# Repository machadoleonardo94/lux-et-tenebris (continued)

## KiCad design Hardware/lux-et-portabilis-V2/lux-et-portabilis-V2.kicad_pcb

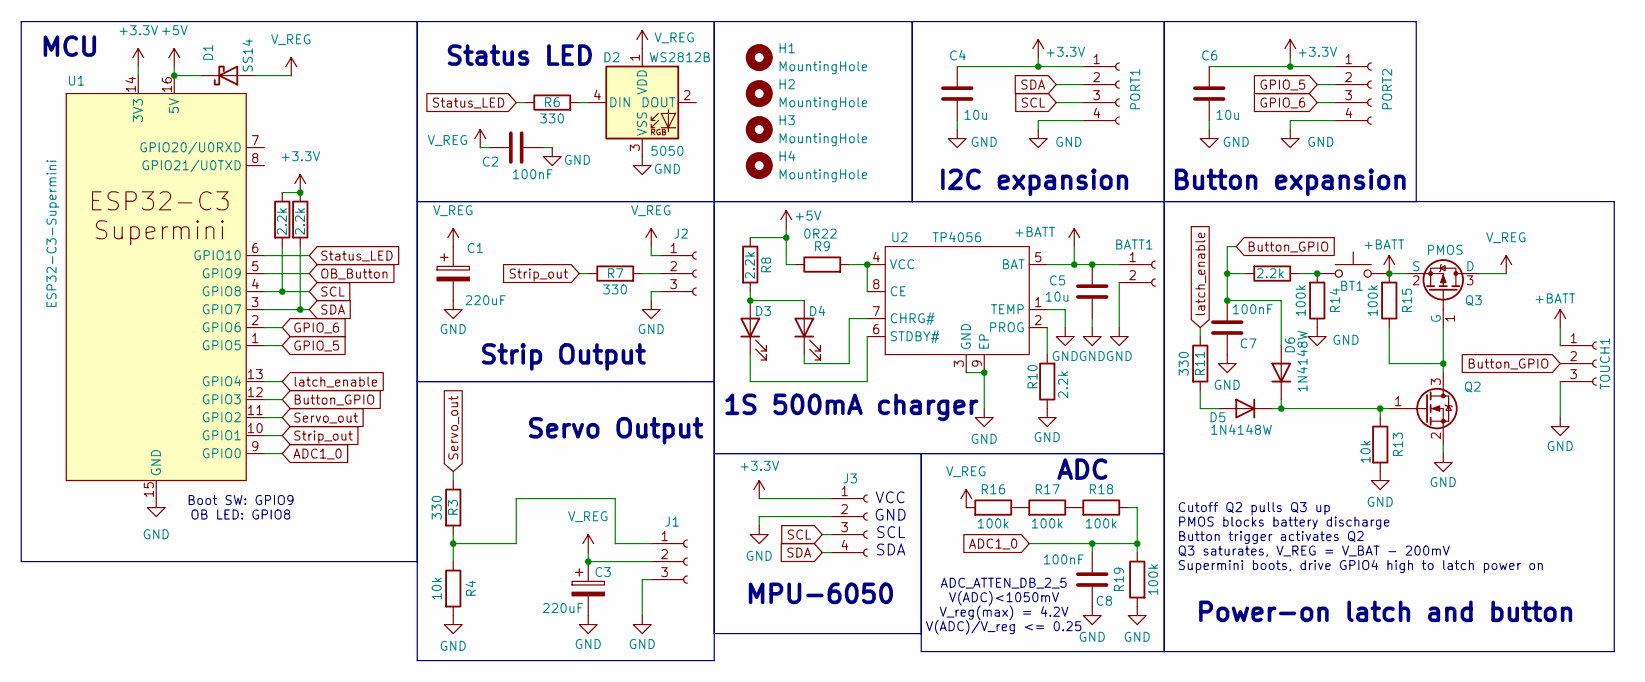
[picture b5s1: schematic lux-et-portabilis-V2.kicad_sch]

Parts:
BATT1: Conn_01x02_Socket; Molex_KK-254_AE-6410-02A_1x02_P2.54mm_Vertical; LCSC C49023803
BT1: SW_Push; SW_SPST_PTS647_Sx38; LCSC C455246
C1, C3: 220uF; CP_Elec_6.3x7.7; Mfr. Part Number 35TKV220M8X10.5; LCSC C25170691
C2, C7, C8: 100nF; C_0805_2012Metric; Mfr. Part Number CC0805KRX7R9BB104; LCSC C49678
C4, C5, C6: 10u; C_0805_2012Metric; LCSC C15850
D1: SS14; D_SMA; LCSC C2480
D2: WS2812B; LED_WS2812B_PLCC4_5.0x5.0mm_P3.2mm; LCSC C2843785
D3: LED_BLUE; LED_0805_2012Metric_Pad1.15x1.40mm_HandSolder; LCSC C965817
D4: LED_RED; LED_0805_2012Metric_Pad1.15x1.40mm_HandSolder; LCSC C84256
D5, D6: 1N4148W; D_SOD-123; Mfr. Part Number 1N4148W-7-F; LCSC C83528
H1, H2, H3, H4: MountingHole; MountingHole_3.2mm_M3
J1: Conn_01x03_Socket; PinHeader_1x03_P2.54mm_Vertical
J2: Conn_01x03_Socket; TerminalBlock_Xinya_XY308-2.54-3P_1x03_P2.54mm_Horizontal
J3: Conn_01x04_Socket; MPU6050
PORT1, PORT2: Conn_01x04_Socket; Hirose_DF13C_CL535-0404-8-51_1x04-1MP_P1.25mm_Vertical; LCSC C7433470
Q2: 2N7002K; SOT-23; LCSC C65189
Q3: PMOS; SOT-23_Handsoldering; LCSC C42456992
R1, R2, R8, R10, R12: 2.2k; R_0805_2012Metric; LCSC C17520
R3, R6, R7, R11: 330; R_0805_2012Metric; LCSC C17630
R4, R13: 10k; R_0805_2012Metric; LCSC C17414
R9: 0R22; R_1206_3216Metric_Pad1.30x1.75mm_HandSolder; LCSC C2683384
R14, R15, R16, R17, R18, R19: 100k; R_0805_2012Metric; LCSC C149504
TOUCH1: Conn_01x03_Socket; PinHeader_1x03_P2.54mm_Vertical
U1: ESP32-C3-Supermini
U2: TP4056; ESOP-8_L4.9-W3.9-P1.27-LS6.0-BL-EP; LCSC Part Name 1A锂电池充电IC

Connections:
+3.3V: C4.1, C6.1, J3.1, PORT1.1, PORT2.1, R1.1, R2.1, U1.14 (3V3)
+5V: D1.1 (K), R8.1, R9.1, U1.16 (5V)
+BATT: BATT1.1, BT1.1, C5.1, Q3.2 (S), R15.2, TOUCH1.1, U2.5 (BAT)
ADC1_0: C8.2, R18.1, R19.1, U1.9 (GPIO0)
Button_GPIO: C7.2, D6.2 (A), R12.2, TOUCH1.2, U1.12 (GPIO3)
GND: BATT1.2, C1.2, C2.2, C3.2, C4.2, C5.2, C6.2, C7.1, C8.1, D2.3 (VSS), J1.3, J2.3, J3.2, PORT1.4, PORT2.4, Q2.2 (S), R4.2, R10.1, R13.2, R14.1, R19.2, TOUCH1.3, U1.15 (GND), U2.1 (TEMP), U2.3 (GND), U2.9 (EP)
GPIO_5: PORT2.2, U1.1 (GPIO5)
GPIO_6: PORT2.3, U1.2 (GPIO6)
unnamed: BT1.2, R12.1, R14.2
unnamed: D2.4 (DIN), R6.2
unnamed: D3.2 (A), D4.2 (A), R8.2
unnamed: D3.1 (K), U2.6 (STDBY#)
unnamed: D4.1 (K), U2.7 (CHRG#)
unnamed: D5.2 (A), R11.2
unnamed: D5.1 (K), D6.1 (K), Q2.1 (G), R13.1
unnamed: J1.1, R3.2, R4.1
unnamed: J2.2, R7.2
unnamed: Q2.3 (D), Q3.1 (G), R15.1
unnamed: R16.1, R17.2
unnamed: R17.1, R18.2
unnamed: R9.2, U2.4 (VCC), U2.8 (CE)
unnamed: R10.2, U2.2 (PROG)
OB_Button: U1.5 (GPIO9)
SCL: J3.3, PORT1.3, R1.2, U1.4 (GPIO8)
SDA: J3.4, PORT1.2, R2.2, U1.3 (GPIO7)
Servo_out: R3.1, U1.11 (GPIO2)
Status_LED: R6.1, U1.6 (GPIO10)
Strip_out: R7.1, U1.10 (GPIO1)
V_REG: C1.1, C2.1, C3.1, D1.2 (A), D2.1 (VDD), J1.2, J2.1, Q3.3 (D), R16.2
latch_enable: R11.1, U1.13 (GPIO4)

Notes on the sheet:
Strip Output
ADC_ATTEN_DB_2_5 V(ADC)<1050mV V_reg(max) = 4.2V V(ADC)/V_reg <= 0.25
I2C expansion
Power-on latch and button
MCU
MPU-6050
Status LED
ADC
Boot SW: GPIO9 OB LED: GPIO8
Cutoff Q2 pulls Q3 up PMOS blocks battery discharge Button trigger activates Q2 Q3 saturates, V_REG = V_BAT - 200mV Supermini boots, drive GPIO4 high to latch power on
1S 500mA charger
Button expansion
Servo Output
VCC GND SCL SDA

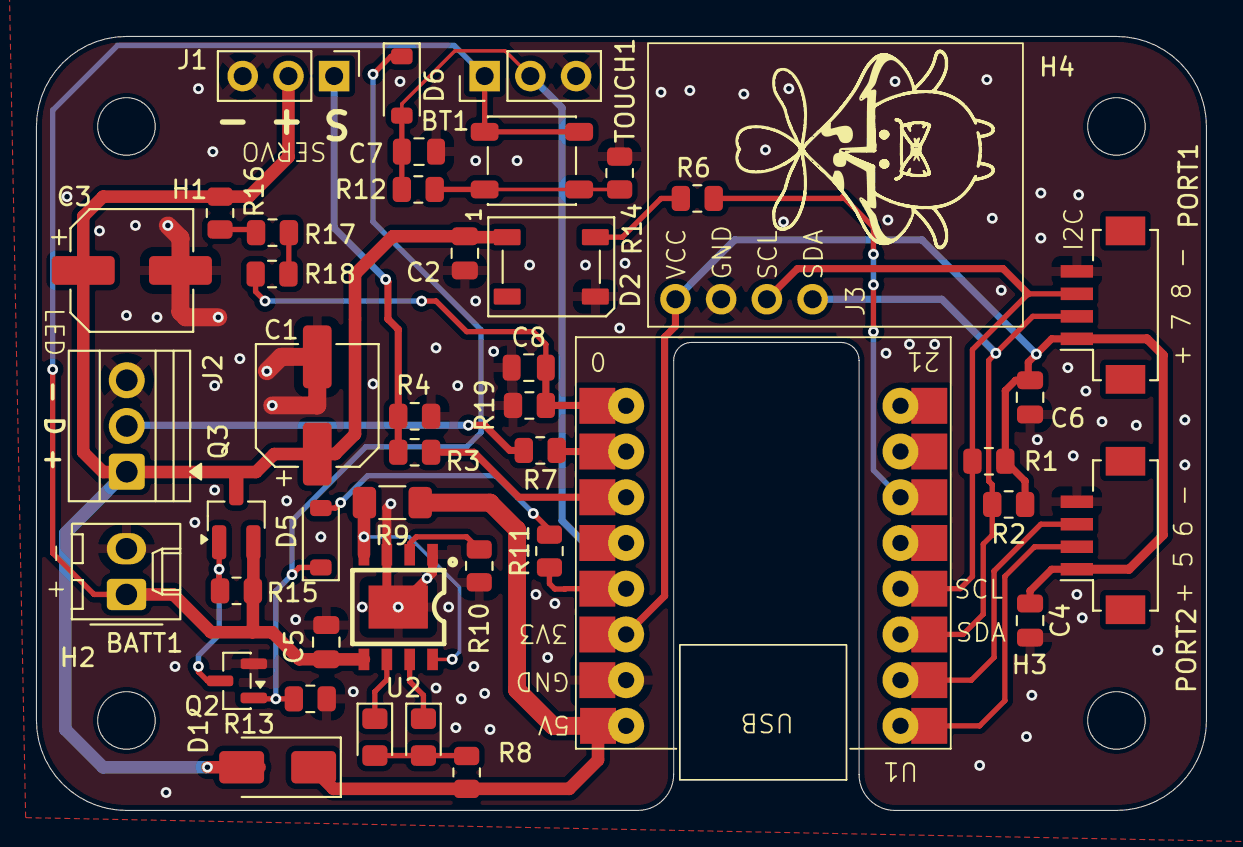
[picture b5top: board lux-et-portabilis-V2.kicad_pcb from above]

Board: 2 copper layers, 65.0 x 43.0 mm, 48 parts (0 on the bottom side), 29 nets.

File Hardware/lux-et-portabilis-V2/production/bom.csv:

Designator,Footprint,Quantity,Value,LCSC Part #
BT1,SW_SPST_PTS647_Sx38,1,SW_Push,C455246
"C1, C3",CP_Elec_6.3x7.7,2,220uF,C25170691
"C2, C7, C8",0805,3,100nF,C49678
"C4, C5, C6",0805,3,10u,C15850
D1,D_SMA,1,SS14,C2480
D2,LED_WS2812B_PLCC4_5.0x5.0mm_P3.2mm,1,WS2812B,C2843785
D3,0805,1,LED_BLUE,C965817
D4,0805,1,LED_RED,C84256
"D5, D6",D_SOD-123,2,1N4148W,C83528
"J1, TOUCH1",PinHeader_1x03_P2.54mm_Vertical,2,Conn_01x03_Socket,
J2,TerminalBlock_Xinya_XY308-2.54-3P_1x03_P2.54mm_Horizontal,1,Conn_01x03_Socket,
J3,MPU6050,1,Conn_01x04_Socket,
"PORT1, PORT2",Hirose_DF13C_CL535-0404-8-51_1x04-1MP_P1.25mm_Vertical,2,Conn_01x04_Socket,C7433470
Q2,SOT-23,1,2N7002K,C65189
Q3,SOT-23_Handsoldering,1,PMOS,C42456992
"R1, R10, R12, R2, R8",0805,5,2.2k,C17520
"R11, R3, R6, R7",0805,4,330,C17630
"R13, R4",0805,2,10k,C17414
"R14, R15, R16, R17, R18, R19",0805,6,100k,C149504
R9,1206,1,0R22,C2683384
U1,ESP32-C3-Supermini,1,ESP32-C3-Supermini,
U2,ESOP-8_L4.9-W3.9-P1.27-LS6.0-BL-EP,1,TP4056,C382139

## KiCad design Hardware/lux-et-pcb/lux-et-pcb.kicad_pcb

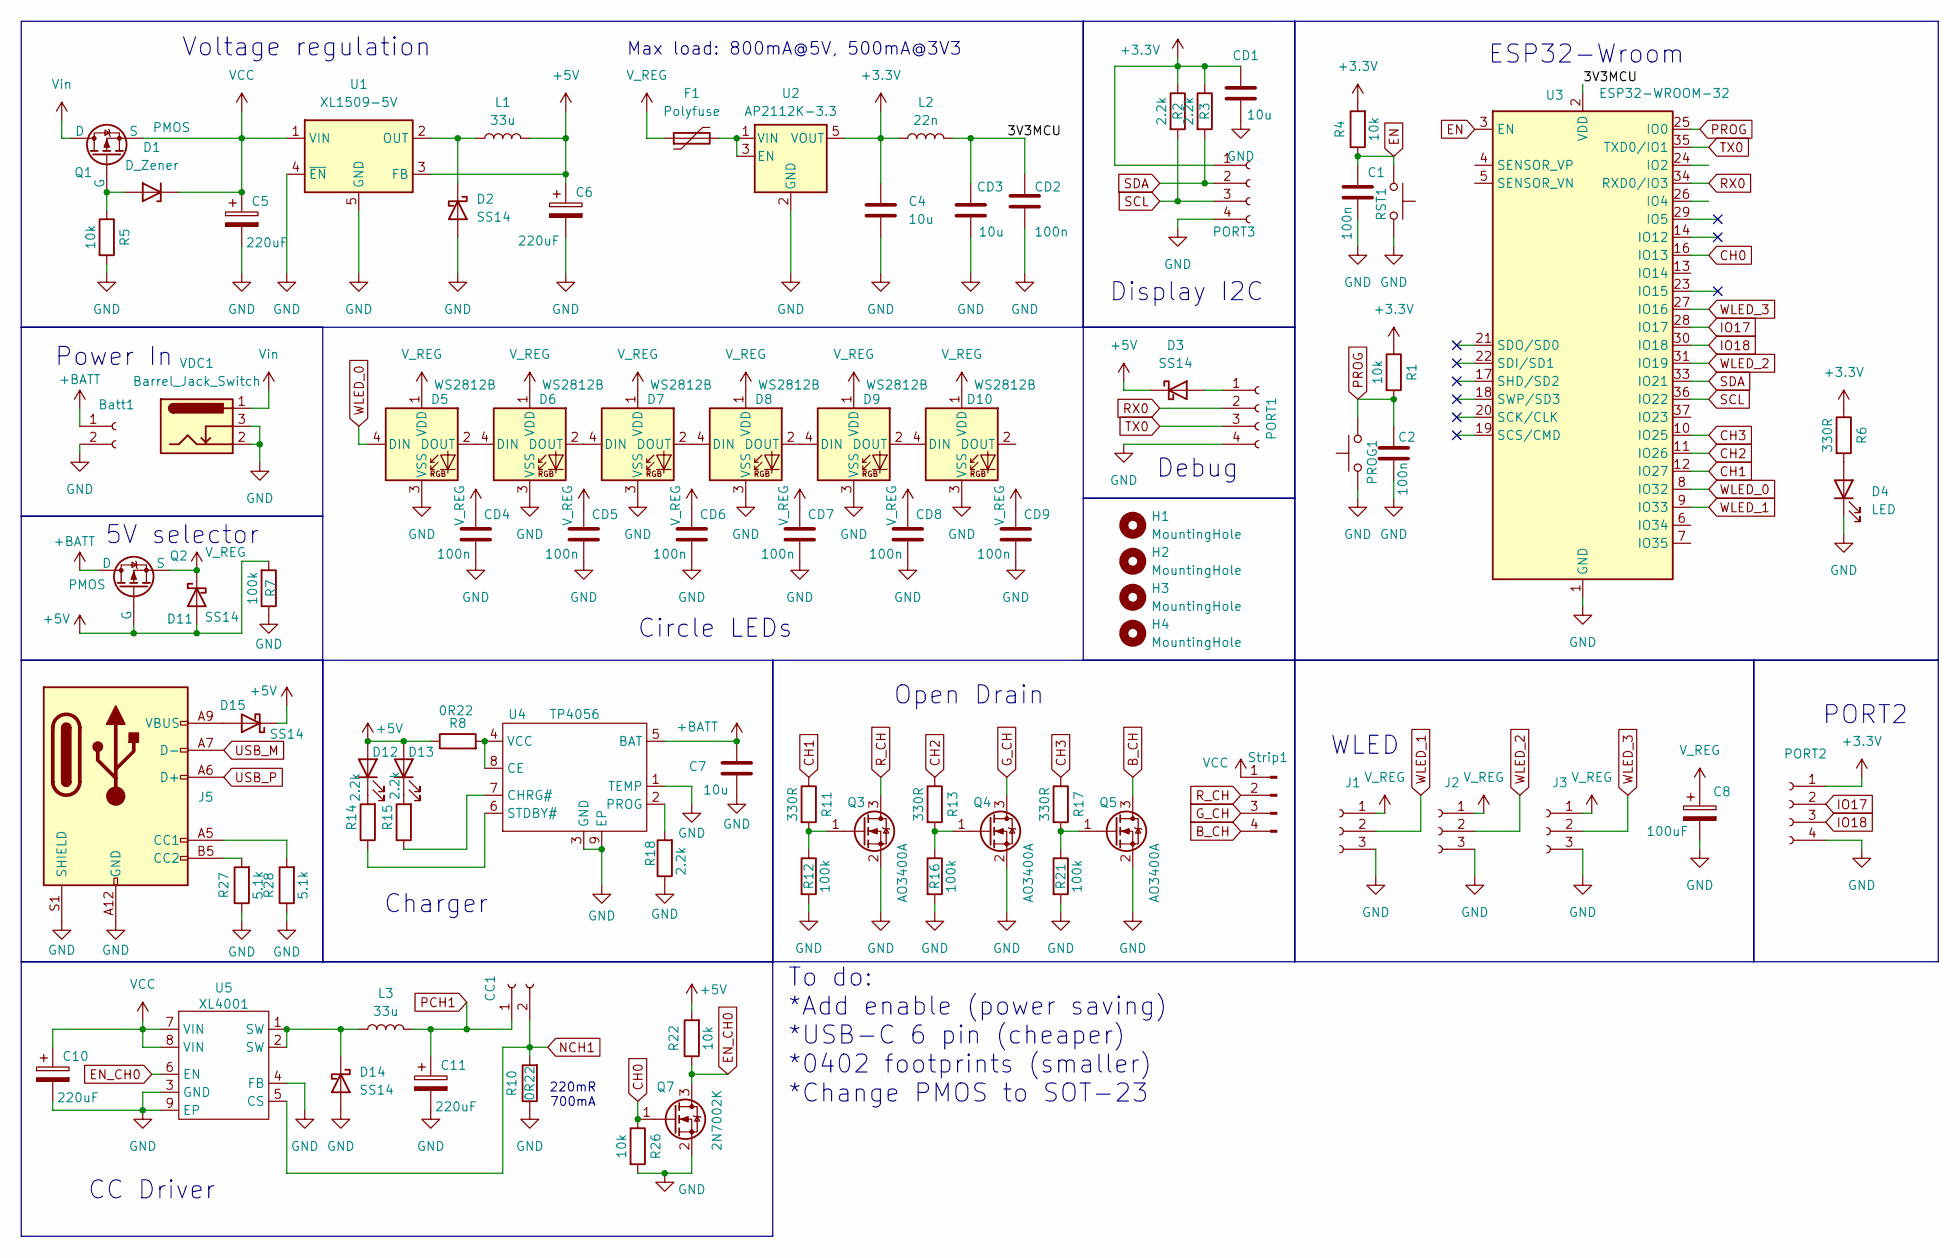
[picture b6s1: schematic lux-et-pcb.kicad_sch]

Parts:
Batt1: Conn_01x02_Socket; Molex_KK-254_AE-6410-02A_1x02_P2.54mm_Vertical; LCSC C49023803
C1, C2: 100n; C_0805_2012Metric; LCSC C2909631
C4, C7: 10u; C_0805_2012Metric; LCSC C380331
C5, C6, C10, C11: 220uF; C_Elec_6.3x7.7; LCSC C7471881
C8: 100uF; C_Elec_6.3x7.7; LCSC C99837
CC1: Conn_01x02_Socket; Molex_KK-254_AE-6410-02A_1x02_P2.54mm_Vertical; LCSC C49023803
CD1, CD3: 10u; C_0805_2012Metric; LCSC C380331
CD2, CD4, CD5, CD6, CD7, CD8, CD9: 100n; C_0805_2012Metric; LCSC C2909631
D1: D_Zener; D_MiniMELF; LCSC C181075
D2, D3, D11, D14, D15: SS14; D_SMA; LCSC C2909920
D4: LED; LED_0805_2012Metric_Pad1.15x1.40mm_HandSolder; LCSC C84256
D5, D6, D7, D8, D9, D10: WS2812B; LED_WS2812B_PLCC4_5.0x5.0mm_P3.2mm; LCSC C2843785
D12: LED_BLUE; LED_0805_2012Metric_Pad1.15x1.40mm_HandSolder; LCSC C965817
D13: LED_RED; LED_0805_2012Metric_Pad1.15x1.40mm_HandSolder; LCSC C84256
F1: Polyfuse; Fuse_1206_3216Metric_Pad1.42x1.75mm_HandSolder; LCSC C22446878
H1, H2, H3, H4: MountingHole; MountingHole_3.2mm_M3
J1, J2, J3: Conn_01x03_Socket; TerminalBlock_Xinya_XY308-2.54-3P_1x03_P2.54mm_Horizontal
J5: USB_C_Receptacle_USB2.0_8P; USB-C-SMD_GT-USB-7101A; LCSC C7469647
L1, L3: 33u; L_Sunlord_SWPA4010S; LCSC C167885
L2: 22n; L_0805_2012Metric; LCSC C108962
PORT1, PORT2, PORT3: Conn_01x04_Socket; Hirose_DF13C_CL535-0404-8-51_1x04-1MP_P1.25mm_Vertical; LCSC C7433470
PROG1: SW_Push; SW_SPST_PTS647_Sx38; LCSC C2888502
Q1, Q2: PMOS; SOT-223-3_TabPin2; LCSC C154901
Q3, Q4, Q5: AO3400A; SOT-23; LCSC C347497
Q7: 2N7002K; SOT-23; LCSC C65189
R1, R4, R5, R22, R26: 10k; R_0805_2012Metric; LCSC C17414
R2, R3, R14, R15, R18: 2.2k; R_0805_2012Metric; LCSC C17520
R6, R11, R13, R17: 330R; R_0805_2012Metric; LCSC C17630
R7, R12, R16, R21: 100k; R_0805_2012Metric; LCSC C149504
R8, R10: 0R22; R_2010_5025Metric; LCSC C2999625
R27, R28: 5.1k; R_0805_2012Metric; LCSC C27834
RST1: SW_Push; SW_SPST_PTS647_Sx38; LCSC C2888502
Strip1: Conn_01x02_Pin; TerminalBlock_Xinya_XY308-2.54-4P_1x04_P2.54mm_Horizontal; LCSC 1
U1: XL1509-5V; SOIC-8_3.9x4.9mm_P1.27mm; LCSC C2681227
U2: AP2112K-3.3; SOT-23-5; LCSC C51118
U3: ESP32-WROOM-32; ESP32-WROOM-32U; LCSC C2980301
U4: TP4056; SOP-8_L4.9-W3.9-P1.27-LS6.0-BL-EP; Manufacturer Part TP4056; LCSC Part Name 1A锂电池充电IC
U5: XL4001; ESOP-8_L4.9-W3.9-P1.27-LS6.0-BL-EP; Manufacturer Part XL4001E1; LCSC Part Name XL4001E1
VDC1: Barrel_Jack_Switch; BarrelJack_Horizontal; LCSC C720557

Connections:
+3.3V: C4.1, CD1.1, L2.1, PORT2.1, PORT3.1, R1.1, R2.1, R3.1, R4.2, R6.1, U2.5 (VOUT)
+5V: C6.1, D3.1 (K), D11.2 (A), D12.2 (A), D13.2 (A), D15.1 (K), L1.2, Q2.2 (G), R7.2, R8.1, R22.2, U1.3 (FB)
+BATT: Batt1.1, C7.1, Q2.1 (D), U4.5 (BAT)
/3V3MCU: CD2.1, CD3.1, L2.2, U3.2 (VDD)
B_CH: Q5.3 (D), Strip1.4
CH0: Q7.1 (G), R26.1, U3.16 (IO13)
CH1: R11.1, U3.12 (IO27)
CH2: R13.1, U3.11 (IO26)
CH3: R17.1, U3.10 (IO25)
EN: C1.1, R4.1, RST1.2, U3.3 (EN)
EN_CH0: Q7.3 (D), R22.1, U5.6 (EN)
GND: Batt1.2, C1.2, C2.2, C4.2, C5.2, C6.2, C7.2, C8.2, C10.2, C11.2, CD1.2, CD2.2, CD3.2, CD4.2, CD5.2, CD6.2, CD7.2, CD8.2, CD9.2, D2.2 (A), D4.1 (K), D5.3 (VSS), D6.3 (VSS), D7.3 (VSS), D8.3 (VSS), D9.3 (VSS), D10.3 (VSS), D14.2 (A), J1.3, J2.3, J3.3, J5.A12 (GND), J5.B12 (GND), J5.S1 (SHIELD), PORT1.4, PORT2.4, PORT3.4, PROG1.1, Q3.2 (S), Q4.2 (S), Q5.2 (S), Q7.2 (S), R5.2, R7.1, R10.1, R12.2, R16.2, R18.1, R21.2, R26.2, R27.1, R28.1, RST1.1, U1.4 (~EN), U1.5 (GND), U1.6 (GND), U1.7 (GND), U1.8 (GND), U2.2 (GND), U3.1 (GND), U3.15 (GND), U3.38 (GND), U3.39 (GND), U4.1 (TEMP), U4.3 (GND), U4.9 (EP), U5.3 (GND), U5.4 (FB), U5.9 (EP), VDC1.2, VDC1.3
G_CH: Q4.3 (D), Strip1.3
IO17: PORT2.2, U3.28 (IO17)
IO18: PORT2.3, U3.30 (IO18)
NCH1: CC1.2, R10.2, U5.5 (CS)
unnamed: D1.2 (A), Q1.2 (G), R5.1
unnamed: D2.1 (K), L1.1, U1.2 (OUT)
unnamed: D3.2 (A), PORT1.1
unnamed: D4.2 (A), R6.2
unnamed: D5.2 (DOUT), D6.4 (DIN)
unnamed: D6.2 (DOUT), D7.4 (DIN)
unnamed: D7.2 (DOUT), D8.4 (DIN)
unnamed: D8.2 (DOUT), D9.4 (DIN)
unnamed: D9.2 (DOUT), D10.4 (DIN)
unnamed: D12.1 (K), R14.2
unnamed: D13.1 (K), R15.2
unnamed: D14.1 (K), L3.1, U5.1 (SW), U5.2 (SW)
unnamed: D15.2 (A), J5.A9 (VBUS), J5.B9 (VBUS)
unnamed: J5.A5 (CC1), R28.2
unnamed: J5.B5 (CC2), R27.2
unnamed: Q3.1 (G), R11.2, R12.1
unnamed: Q4.1 (G), R13.2, R16.1
unnamed: Q5.1 (G), R17.2, R21.1
unnamed: F1.2, U2.1 (VIN), U2.3 (EN)
unnamed: R8.2, U4.4 (VCC), U4.8 (CE)
unnamed: R15.1, U4.7 (CHRG#)
unnamed: R18.2, U4.2 (PROG)
unnamed: R14.1, U4.6 (STDBY#)
PCH1: C11.1, CC1.1, L3.2
PROG: C2.1, PROG1.2, R1.2, U3.25 (IO0)
RX0: PORT1.2, U3.34 (RXD0/IO3)
R_CH: Q3.3 (D), Strip1.2
SCL: PORT3.3, R2.2, U3.36 (IO22)
SDA: PORT3.2, R3.2, U3.33 (IO21)
TX0: PORT1.3, U3.35 (TXD0/IO1)
USB_M: J5.A7 (D-)
USB_P: J5.A6 (D+)
VCC: C5.1, C10.1, D1.1 (K), Q1.3 (S), Strip1.1, U1.1 (VIN), U5.7 (VIN), U5.8 (VIN)
V_REG: C8.1, CD4.1, CD5.1, CD6.1, CD7.1, CD8.1, CD9.1, D5.1 (VDD), D6.1 (VDD), D7.1 (VDD), D8.1 (VDD), D9.1 (VDD), D10.1 (VDD), D11.1 (K), F1.1, J1.1, J2.1, J3.1, Q2.3 (S)
Vin: Q1.1 (D), VDC1.1
WLED_0: D5.4 (DIN), U3.8 (IO32)
WLED_1: J1.2, U3.9 (IO33)
WLED_2: J2.2, U3.31 (IO19)
WLED_3: J3.2, U3.27 (IO16)

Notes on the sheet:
Debug
To do: *Add enable (power saving) *USB-C 6 pin (cheaper) *0402 footprints (smaller) *Change PMOS to SOT-23
PORT2
220mR 700mA
Voltage regulation
Open Drain
ESP32-Wroom
5V selector
Display I2C
Power In
Max load: 800mA@5V, 500mA@3V3
CC Driver
Circle LEDs
Charger
WLED

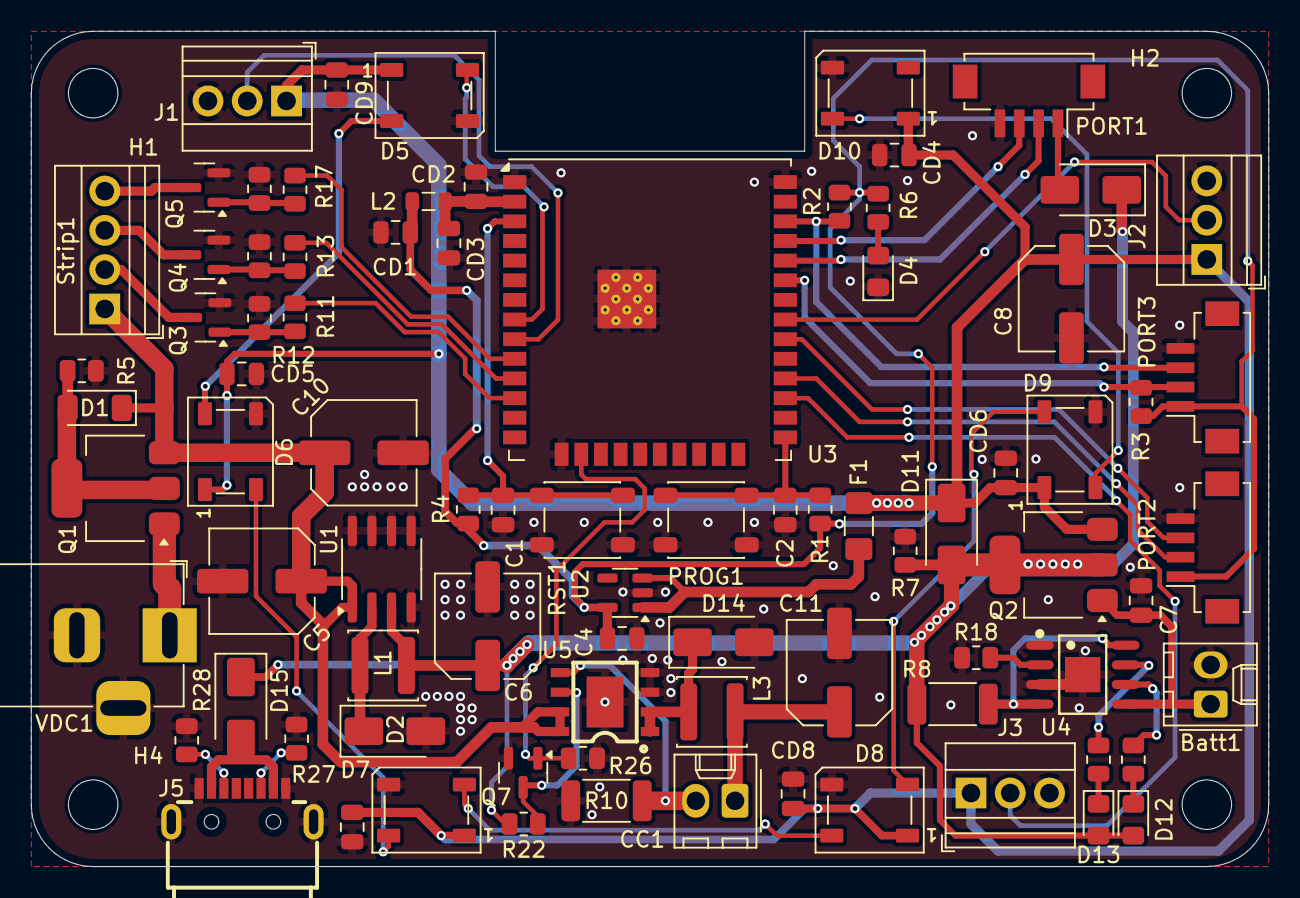
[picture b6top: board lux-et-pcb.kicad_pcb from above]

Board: 2 copper layers, 80.0 x 54.0 mm, 87 parts (0 on the bottom side), 53 nets.

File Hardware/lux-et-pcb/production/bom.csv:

Designator,Footprint,Quantity,Value,LCSC Part #
"BATT1, CC1",Molex_KK-254_AE-6410-02A_1x02_P2.54mm_Vertical,2,Conn_01x02_Socket,C49023803
"C1, C2, CD2, CD4, CD5, CD6, CD7, CD8, CD9",0805,9,100n,C2909631
"C10, C11, C5, C6",C_Elec_6.3x7.7,4,220uF,C7471881
"C4, C7, CD1, CD3",0805,4,10u,C380331
C8,C_Elec_6.3x7.7,1,100uF,C99837
D1,D_MiniMELF,1,D_Zener,C181075
"D10, D5, D6, D7, D8, D9",LED_WS2812B_PLCC4_5.0x5.0mm_P3.2mm,6,WS2812B,C2843785
"D11, D14, D15, D2, D3",D_SMA,5,SS14,C2909920
D12,0805,1,LED_BLUE,C965817
D13,0805,1,LED_RED,C84256
D4,0805,1,LED,C84256
F1,1206,1,Polyfuse,C22446878
"J1, J2, J3",TerminalBlock_Xinya_XY308-2.54-3P_1x03_P2.54mm_Horizontal,3,Conn_01x03_Socket,
J5,USB-C-SMD_GT-USB-7101A,1,USB_C_Receptacle_USB2.0_8P,C7469647
"L1, L3",L_Sunlord_SWPA4010S,2,33u,C167885
L2,0805,1,22n,C108962
"PORT1, PORT2, PORT3",Hirose_DF13C_CL535-0404-8-51_1x04-1MP_P1.25mm_Vertical,3,Conn_01x04_Socket,C7433470
"PROG1, RST1",SW_SPST_PTS647_Sx38,2,SW_Push,C2888502
"Q1, Q2",SOT-223-3_TabPin2,2,PMOS,C154901
"Q3, Q4, Q5",SOT-23,3,AO3400A,C347497
Q7,SOT-23,1,2N7002K,C65189
"R1, R22, R26, R4, R5",0805,5,10k,C17414
"R10, R8",2010,2,0R22,C2999625
"R11, R13, R17, R6",0805,4,330,C17630
"R12, R16, R21, R7",0805,4,100k,C149504
"R14, R15",0805,2,1k,C11702
"R18, R2, R3",0805,3,2k2,C17520
"R27, R28",0805,2,5.1k,C27834
STRIP1,TerminalBlock_Xinya_XY308-2.54-4P_1x04_P2.54mm_Horizontal,1,Conn_01x02_Pin,1
U1,SOIC-8_3.9x4.9mm_P1.27mm,1,XL1509-5V,C2681227
U2,SOT-23-5,1,AP2112K-3.3,C51118
U3,ESP32-WROOM-32U,1,ESP32-WROOM-32,C2980301
U4,SOP-8_L4.9-W3.9-P1.27-LS6.0-BL-EP,1,TP4056,C382139
U5,ESOP-8_L4.9-W3.9-P1.27-LS6.0-BL-EP,1,~,C2988027
VDC1,BarrelJack_Horizontal,1,Barrel_Jack_Switch,C720557

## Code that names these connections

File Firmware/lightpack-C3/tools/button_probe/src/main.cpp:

//? ---------------------- BUTTON PROBE ----------------------
//? A diagnostics-only sketch for the Lux et Portabilis V2 button net.
//? Build and flash it with, from the firmware directory:
//?     pio run -d tools/button_probe -t upload --upload-port COM6
//? It is NOT part of the firmware: this directory is its own PlatformIO project
//* (see platformio.ini here), so the real firmware is not compiled into it.

//! WHY THIS EXISTS
//! The touch pad is an EXTERNAL module on TOUCH1, and the V2 board puts no pull
//! resistor on that net. Measured off the board's own net table:
//!
//!   TOUCH1 pin 1 -> +BATT          (the raw battery rail, NOT 3.3 V)
//!   TOUCH1 pin 2 -> Button_GPIO    (the module's OUT)
//!   TOUCH1 pin 3 -> GND
//!   Button_GPIO  -> ESP32-C3 pad 12 = GPIO3, and nothing else drives it:
//!                   C7  100 nF to GND   (filter)
//!                   R12 2.2 k to BT1    (the on-board power button shares this net)
//!                   D6  1N4148W         (clamp, anode on this net)
//!
//! So the idle level of GPIO3 is entirely the module's business. The firmware
//! assumes ACTIVE HIGH - button_input_configure() gives it INPUT_PULLDOWN and
//* setup_button_interrupt() waits for a RISING edge. A module that is active-LOW
//! or open-drain can never produce that rising edge, and the button then looks
//* completely dead while being perfectly wired.

//! HOW TO READ THIS
//! Each pin is sampled for PROBE_WINDOW_MS under three internal pull
//! configurations in turn. Every window reports the digital levels seen, how many
//! times the level changed, and the average ADC reading in millivolts.
//!
//! Touch the module during EVERY window, then compare:
//!
//!   Only the PULLDOWN window shows edges, min=0 max=1
//!       -> active HIGH, push-pull. The firmware's assumption is correct and the
//!          fault is elsewhere (power to the module, or the module itself).
//!
//!   Only the PULLUP window shows edges, min=0 max=1
//!       -> active LOW / open drain. The firmware needs active_high = false,
//!          which also switches it to INPUT_PULLUP (see services/readings.h).
//!
//!   Edges in NO window, level pinned at 0 or 1
//!       -> the pin never moves. The module is unpowered, its OUT is not on
//!          TOUCH1 pin 2, or it is dead. Check VCC at TOUCH1 pin 1 - remember it
//!          is +BATT, so on USB with no cell fitted it may not be what you expect.
//!
//!   Every window wanders between 0 and 1 with no touch, and the average ADC
//!   reading drifts when your hand approaches
//!       -> nothing is attached to that pin. It is floating.
//!
//!   A fixed average near 1650 mV that never reaches 0 or 3.3 V
//!       -> two resistors are fighting over the line. That is the signature of an
//!          external pull meeting the internal one, and it explains a pin that
//!          reads a constant HIGH or LOW no matter what the module does.
//!
//! GPIO2 is probed as well, as a CONTROL. On this board pad 11 is Servo_out, so
//? it is expected to look like nothing or like a floating pin - it is there to
//* show what "no button here" looks like next to the real pin.

//! SAFETY - GPIO4
//! GPIO4 is latch_enable: it holds the board's own power latch closed. The real
//! firmware raises it in the first statements of setup(), and this sketch does the
//! same. Without it the latch opens and the board switches itself off as soon as
//* the power button is released, which looks exactly like a crash.

#include <Arduino.h>

#define LATCH_ENABLE_PIN 4
#define BUTTON_PIN 3 // TOUCH1 pin 2, the module's OUT, shared with BT1 through R12
#define CONTROL_PIN 2 // Servo_out on V2 - no button here, for contrast

//* How long each pull configuration is held before the report moves on.
#define PROBE_WINDOW_MS 2000
//* Sampling period inside a window. 2 ms is well under any module's output
//* transition and gives ~1000 samples per window.
#define PROBE_SAMPLE_MS 2
//* Discarded after a configuration change: the pin and the 100 nF cap on it need
//! a moment to settle, and those samples would be counted as edges otherwise.
#define PROBE_SETTLE_MS 40

enum probePull : uint8_t
{
    PULL_FLOAT = 0,
    PULL_UP,
    PULL_DOWN,
    PULL_COUNT
};

const char *pull_name(uint8_t cfg)
{
    switch (cfg)
    {
    case PULL_FLOAT:
        return "float   ";
    case PULL_UP:
        return "pullup  ";
    default:
        return "pulldown";
    }
}

void probe_apply_pull(uint8_t pin, uint8_t cfg)
{
    switch (cfg)
    {
    case PULL_UP:
        pinMode(pin, INPUT_PULLUP);
        break;
    case PULL_DOWN:
        pinMode(pin, INPUT_PULLDOWN);
        break;
    default:
        //? INPUT, not INPUT_PULLUP: this window has to show what the outside
        //* world does with the pin when nothing on the chip helps it.
        pinMode(pin, INPUT);
        break;
    }
}

//* One window: hold one pull configuration and report what the pin did.
//? `edges` is the count of digital level changes, so a pin that follows the
//? module produces edges in the window whose pull matches the module's idle
//* state, and a pin that never moves produces none anywhere.
void probe_window(uint8_t pin, uint8_t cfg)
{
    probe_apply_pull(pin, cfg);
    delay(PROBE_SETTLE_MS);

    int first = digitalRead(pin);
    int sawLow = (first == LOW) ? 1 : 0;
    int sawHigh = (first == HIGH) ? 1 : 0;
    int edges = 0;
    int previous = first;

    uint32_t samples = 0;
    uint32_t mv_sum = 0;

    const uint32_t start = millis();
    while (millis() - start < (uint32_t)PROBE_WINDOW_MS)
    {
        const int level = digitalRead(pin);
        if (level != previous)
        {
            edges++;
            previous = level;
        }
        if (level == LOW)
            sawLow = 1;
        else
            sawHigh = 1;

        //? analogReadMilliVolts() applies the core's own eFuse calibration, so
        //* this figure is directly comparable to a multimeter on the pin - which
        //? is what makes a "stuck at 1.65 V" divider visible as such instead of
        //* just reading as a solid HIGH.
        mv_sum += (uint32_t)analogReadMilliVolts(pin);
        samples++;

        delay(PROBE_SAMPLE_MS);
    }

    const uint32_t avg_mv = (samples > 0) ? (mv_sum / samples) : 0;

    Serial.printf("[PROBE] GPIO%-2u %s  low=%d high=%d edges=%-4d avg=%4u mV\n",
                  (unsigned)pin, pull_name(cfg), sawLow, sawHigh, edges,
                  (unsigned)avg_mv);
}

void probe_pin(uint8_t pin, const char *note)
{
    Serial.printf("\n[PROBE] ===== GPIO%u %s =====\n", (unsigned)pin, note);
    for (uint8_t cfg = 0; cfg < PULL_COUNT; cfg++)
        probe_window(pin, cfg);
}

void setup()
{
    //* First, for the reason in the header: the power latch is the board's own
    //* supply and nothing else in this sketch would keep it closed.
    pinMode(LATCH_ENABLE_PIN, OUTPUT);
    digitalWrite(LATCH_ENABLE_PIN, HIGH);

    Serial.begin(115200);
    delay(300);

    Serial.println("\n\n================ BUTTON PROBE ================");
    Serial.println("Lux et Portabilis V2 - touch module polarity test");
    Serial.println("TOUCH1: pin1=+BATT  pin2=signal  pin3=GND");
    Serial.println("GPIO3 is the button net. GPIO2 is Servo_out, used as a control.");
    Serial.println("");
    Serial.println("Touch the module during EVERY window below.");
    Serial.println("  edges in PULLDOWN only -> active HIGH (firmware's assumption)");
    Serial.println("  edges in PULLUP only   -> active LOW  (firmware must invert)");
    Serial.println("  edges nowhere          -> module unpowered / not on pin 2 / dead");
    Serial.println("  wanders with no touch  -> nothing attached to that pin");
    Serial.printf("\nEach window is %u ms.\n", (unsigned)PROBE_WINDOW_MS);
}

void loop()
{
    probe_pin(BUTTON_PIN, "(TOUCH1 pin 2, the button)");
    probe_pin(CONTROL_PIN, "(Servo_out, control - no button expected)");

    Serial.println("\n[PROBE] ---- cycle complete, repeating ----");
}

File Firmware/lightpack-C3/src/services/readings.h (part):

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        return;
    lastUpdate = millis();
    //! `analog_channel_0` is both the ADC1 channel index and the GPIO number: on
    //! the C3 that pin is GPIO0 = ADC1_CH0. analogRead() wants the PIN, and here
    //! the two agree. This call used to name `adc_input`, which is defined
    //! nowhere.
    adcReading = analogRead(analog_channel_0);
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    //! oneshot driver. Reinstating the legacy esp_adc_cal_* API here would abort
    //! the board - see the note in components/ESP32/setup.h.
    //* The board divides the rail by 4 before it reaches the pin (pinout.h:
    //* V(ADC)/V_reg <= 0.25), so 4x the pin voltage is the rail.
    adcVoltage = 4 * analogReadMilliVolts(analog_channel_0);
    Serial.printf("[ADC] Reading: %d, Voltage: %d mV\n", adcReading, adcVoltage);
}
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//! open. It also cannot tell USB from battery, because V_REG sits at the battery
//? voltage in both cases. What it is, is the LED rail, which is precisely the
//* node that matters here: the external strip, the onboard pixel and the
//? module's own 5V pin all hang off V_REG, separated only by the SS14 at D1.
//* Conversions averaged per supply_rail_mv() call.
#define SUPPLY_RAIL_SAMPLES 8

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//? Two switches on this board, both reported live on the configuration page (the
//? table below is what webpage_handle_buttons() walks):
//?
//?   touch_button  GPIO3  The touch module. It drives the pin HIGH while it is
//!                        touched. HARDWARE DAMAGED on this board: the pad still
//?                        measures a clean 3.3 V but the pin reads LOW and never
//!                        latches an edge, so nothing here fires any more. Kept
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//! The V2 board's net table reads:
//?
//?   TOUCH1 pin 1 -> +BATT          the raw battery rail, NOT 3.3 V
//?   TOUCH1 pin 2 -> Button_GPIO    the module's OUT
//?   TOUCH1 pin 3 -> GND
//?   Button_GPIO  -> GPIO3 (SuperMini pad 12), shared with the on-board power
//?                   button BT1 through R12 (2.2k), filtered by C7 (100nF to GND)
//?
//! There is NO pull-up and NO pull-down anywhere on that net. The idle level is
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#define BUTTON_POWER_HOLD_MS 5000  // Touch held past this: latch off, power down

//* ---------------------- BOOT BUTTON GESTURES ----------------------
//? Every user-facing gesture now lives on ONE switch, GPIO9, because GPIO3 is
//! hardware-damaged on this board (the input buffer stopped responding while the
//? pad still measured a clean 3.3 V). GPIO9 is on the SuperMini module itself, so
//* it survives any repair done to the carrier board.
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
void setup_button_interrupt()
{
    //* GPIO3, the touch module. The edge is derived from the flag below instead of
    //? being fixed at RISING, because active_high already owns the pull and
    //? button_is_down() - and an ISR watching the wrong edge is the one failure
    //! that is indistinguishable from dead hardware (see TOUCH MODULE POLARITY
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    //? The touch button has no recovery hold: the 0 below says so, and the pair
    //* that follows is its action threshold and its monitor timeout, which are the
    //* same number by design.
    button_input_configure(touch_button, button_pin, true, "touch", "Touch button (GPIO3)",
                           "1 s press: next LED mode. 5 s press: power off at the latch.",
                           "power off",
                           BUTTON_LONG_PRESS_MS, BUTTON_POWER_HOLD_MS, 0,
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    attachInterrupt(digitalPinToInterrupt(touch_button.pin), touch_button_isr,
                    touch_button.active_high ? RISING : FALLING);

    //! GPIO9 is the C3's BOOT strap pin, not GPIO0: the comment that used to sit
    //! here described the classic ESP32 board this firmware was ported from. The
    //! Supermini pulls it up, so the switch reads HIGH when idle and LOW while it
    //! is held - which is what the pressed/released test and the flag-derived
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
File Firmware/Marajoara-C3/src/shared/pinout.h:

//? ------------------------------------------------------------------------------------------
//*! This file contains all the hardware pinout definitions for the project.
//? ------------------------------------------------------------------------------------------

#ifndef PROJECT_GLOBAL_PINOUT
#define PROJECT_GLOBAL_PINOUT

//* ADC:
#define adc_0 0

//* Channels:
#define strip_out 1
#define majora_out 2

//* Touch:
#define button 3

//* Latch power on
#define latch_enable 4

//* PORT3 (free GPIOs):
#define freeGPIOA 5
#define freeGPIOB 6

//* PORT1 (I2C pins):
#define i2c_sda 7
#define i2c_scl 8

#define prog_switch GPIO_NUM_9 // Switch on C3 Supermini devboard

//* Unrouted (Serial0):
#define tx_0 20
#define rx_0 21

#endif // PROJECT_GLOBAL_PINOUT

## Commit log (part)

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2025-10-07 Added base hardware
    Missing trimpot footprint
2025-10-08 Minor update
2025-10-08 Current hardware update
2025-10-10 First finished layout for review
2025-10-11 Yet another version for review before fabrication
2025-10-15 Updated fabrication files
2025-10-22 Added base firmware
2025-10-22 BoM update
2025-10-25 Added V2 placeholder sketch
2025-11-19 Hardware update
2025-11-19 Added ring animation
2025-11-20 Added deep sleep on prog long press
2025-11-20 Prettify circle LED animation
2025-11-20 Update on case
2025-11-21 Flashes green on boot
2025-11-21 Less stupid deep sleep call
2025-11-21 Added macro for ring light
2025-11-21 Case update
2025-12-03 Added Majoras initial script, Readme.h and power output pins.
2025-12-03 Readme hotfix
2025-12-04 Added WiFi toggle and animations for connected and not connected to the WiFi
2025-12-05 Added V2 base sketch
2025-12-05 Added media for application examples
2025-12-05 Added media for firmware description
2025-12-05 Added Clanker fix so the video should be streamed now
2025-12-05 Fixed Clanker's fuckup on media
    I've researched the correct way to implement the embedded media feature, wich can be understood at https://i.sstatic.net/vxyiV.gif
2025-12-05 Added hardware base readme
2025-12-05 Revise GPIO details and project opening instructions
    Mostly formatting, and adding a fix image for a problem
2025-12-05 Added intro readme.md
2025-12-05 Moved Clanker's disclaimer from firmware to main readme.md
2026-01-13 First working sketch for Esphome
2026-02-26 Added base 8266 12F sketch
2026-03-05 Added base hardware for smaller version
2026-03-05 Added fabrication files
2026-03-05 Update on fabrication files
    Added serial header
2026-03-06 Fabrication files update
    Removed copper fill near WiFi antenna
2026-03-10 Hardware and firmware update
2026-03-11 Boot switch added, with connector for touch sensor
2026-03-17 Fabrication files for Lux et Portabilis V2
    Added power saving by shutting down the battery
    Added onboard boot button
2026-03-18 Added ADC reading to Portabilis V2
    Plus board render
    Changed Status LED pin to GPIO10
2026-03-18 Added power latch explanation
2026-03-23 Basic C3 firmware for Lux et Portabilis
2026-03-23 Added 5mm LED pcb adapter
2026-03-23 Added step files and stencil holder
2026-03-24 Added printed case files and basic gyro support
2026-03-28 Added base Castorice firmware
2026-03-29 updates hehe
2026-04-06 Added base Majora sketches
2026-04-06 Marajoara update
2026-04-07 Fabrication files for Marajoara
    Plus Xunxo Portabilis, to mend old hardware onto new frame
2026-04-11 Added Marajoara V2 - ESP32 + I2S Audio
2026-04-11 Fabricated PCB files
2026-05-04 Added Echoes of Termina base firmware
2026-05-12 Added base Marajoara firmware
2026-05-22 Added base C3V2 sketch
2026-06-27 Updates for Geo and Electro vision PCBs
